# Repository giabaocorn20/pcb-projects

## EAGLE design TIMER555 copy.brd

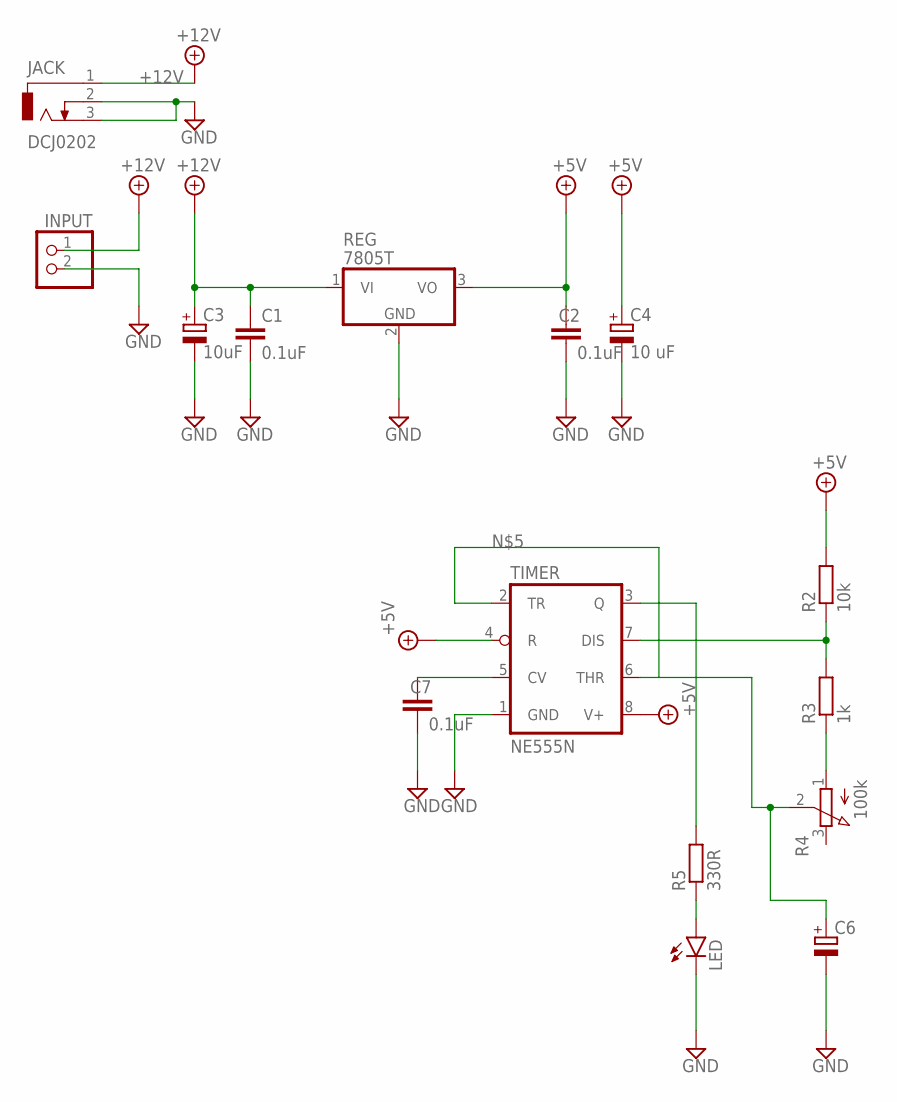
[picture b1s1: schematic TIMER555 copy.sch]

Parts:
C1, C2, C7: 0.1uF; C050-030X075
C3: 10uF; E3,5-8
C4: 10 uF; E3,5-8
C6: CPOL-EUE3.5-8; E3,5-8
INPUT: PINHD-1X2; 1X02
JACK: DCJ0202
LED: LED5MM
R2: 10k; 0207/10
R3: 1k; 0207/10
R4: 100k; 3RP/1610N
R5: 330R; 0207/10
REG: 7805T; TO220H
TIMER: NE555N; DIL08

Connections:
+5V: C2.1, C4.+, R2.2, REG.3 (VO), TIMER.4 (R), TIMER.8 (V+)
+12V: C1.1, C3.+, INPUT.1, JACK.1, REG.1 (VI)
GND: C1.2, C2.2, C3.-, C4.-, C6.-, C7.2, INPUT.2, JACK.2, JACK.3, LED.K (C), REG.2 (GND), TIMER.1 (GND)
unnamed: C7.1, TIMER.5 (CV)
unnamed: R2.1, R3.2, TIMER.7 (DIS)
unnamed: R3.1, R4.1 (A)
unnamed: C6.+, R4.2 (S), TIMER.2 (TR), TIMER.6 (THR)
unnamed: R5.2, TIMER.3 (Q)
unnamed: LED.A, R5.1

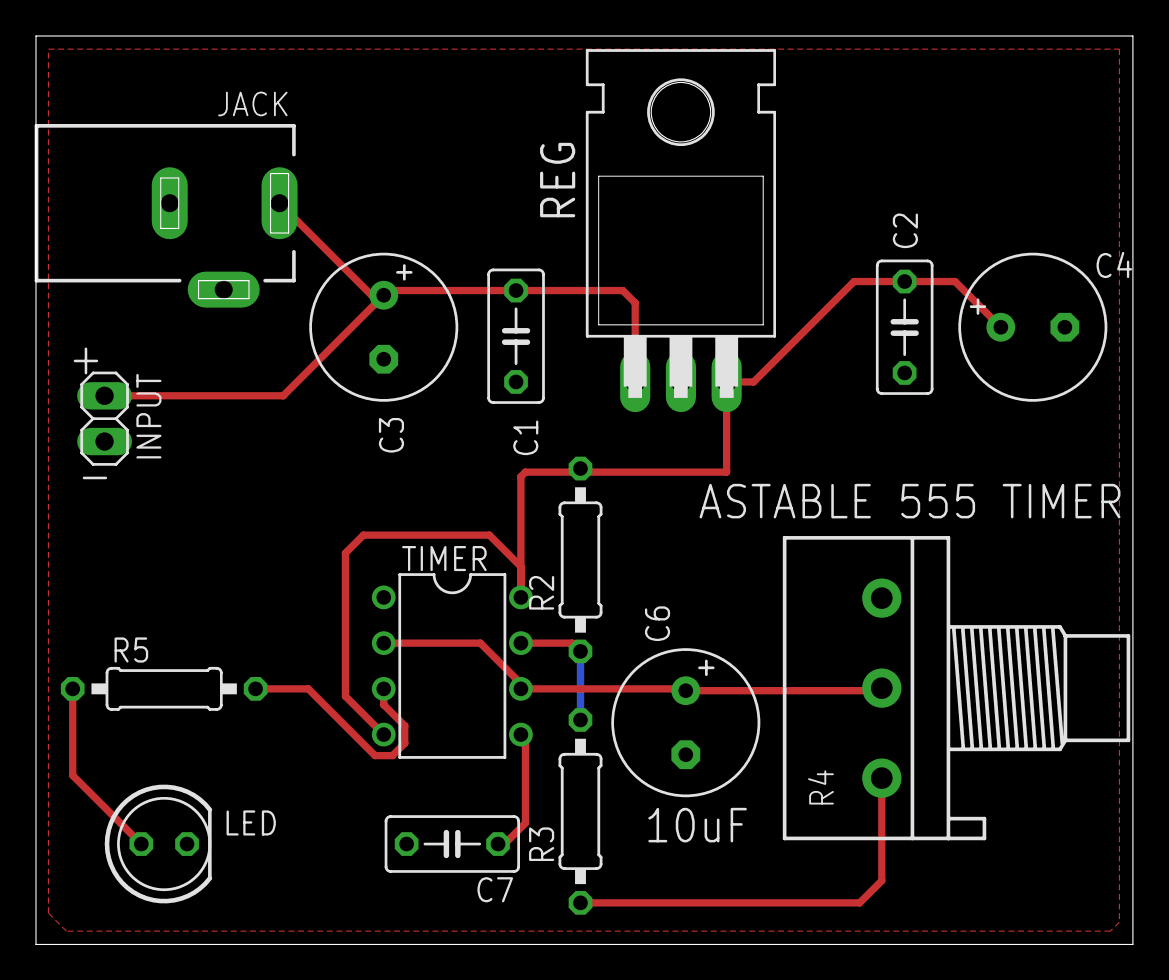
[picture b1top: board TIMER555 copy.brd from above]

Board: 2 copper layers, 60.9 x 50.5 mm, 15 parts (0 on the bottom side), 9 nets.

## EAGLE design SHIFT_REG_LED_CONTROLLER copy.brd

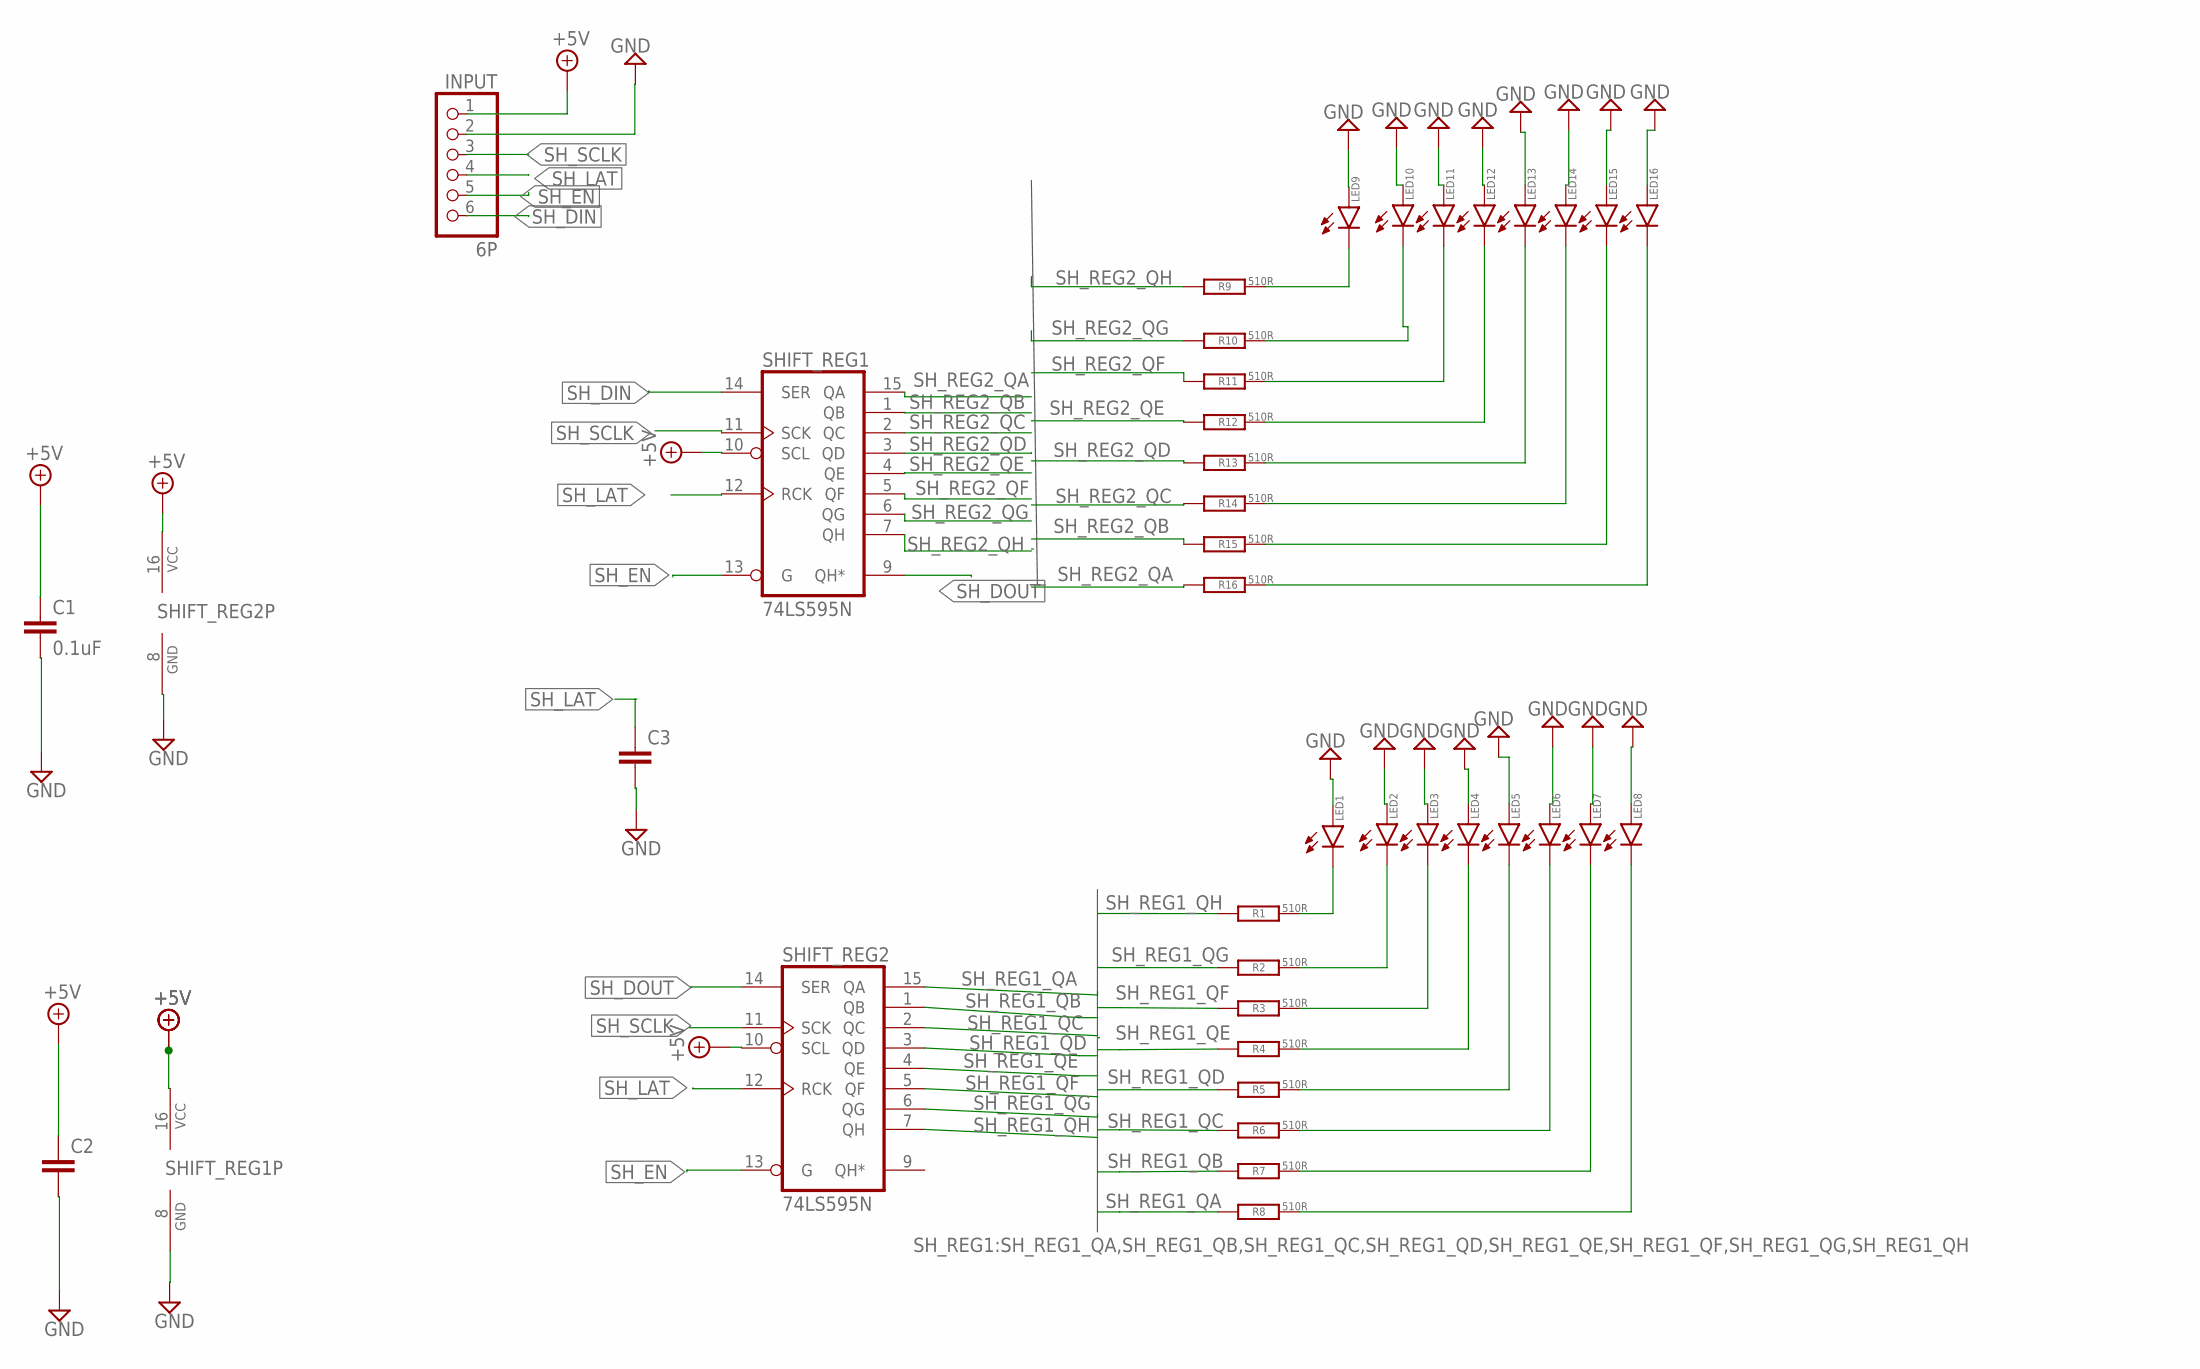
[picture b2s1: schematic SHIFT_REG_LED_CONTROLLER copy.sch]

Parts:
C1: 0.1uF; C050-030X075
C2, C3: C-EU050-030X075; C050-030X075
INPUT: 6P; 1X06
LED1, LED2, LED3, LED4, LED5, LED6, LED7, LED8, LED9, LED10, LED11, LED12, LED13, LED14, LED15, LED16: LED5MM
R1, R2, R3, R4, R5, R6, R7, R8, R9, R10, R11, R12, R13, R14, R15, R16: 510R; 0207/10
SHIFT_REG1, SHIFT_REG2: 74LS595N; DIL16

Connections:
+5V: C1.1, C2.1, INPUT.1, SHIFT_REG1.10 (SCL), SHIFT_REG1.16 (VCC), SHIFT_REG2.10 (SCL), SHIFT_REG2.16 (VCC)
GND: C1.2, C2.2, C3.2, INPUT.2, LED1.A, LED2.A, LED3.A, LED4.A, LED5.A, LED6.A, LED7.A, LED8.A, LED9.A, LED10.A, LED11.A, LED12.A, LED13.A, LED14.A, LED15.A, LED16.A, SHIFT_REG1.8 (GND), SHIFT_REG2.8 (GND)
unnamed: LED1.K (C), R1.2
unnamed: LED2.K (C), R2.2
unnamed: LED3.K (C), R3.2
unnamed: LED4.K (C), R4.2
unnamed: LED5.K (C), R5.2
unnamed: LED6.K (C), R6.2
unnamed: LED7.K (C), R7.2
unnamed: LED8.K (C), R8.2
unnamed: LED9.K (C), R9.2
unnamed: LED10.K (C), R10.2
unnamed: LED11.K (C), R11.2
unnamed: LED12.K (C), R12.2
unnamed: LED13.K (C), R13.2
unnamed: LED14.K (C), R14.2
unnamed: LED15.K (C), R15.2
unnamed: LED16.K (C), R16.2
SH_DIN: INPUT.6, SHIFT_REG1.14 (SER)
SH_DOUT: SHIFT_REG1.9 (QH*), SHIFT_REG2.14 (SER)
SH_EN: INPUT.5, SHIFT_REG1.13 (G), SHIFT_REG2.13 (G)
SH_LAT: C3.1, INPUT.4, SHIFT_REG1.12 (RCK), SHIFT_REG2.12 (RCK)
SH_REG1_QA: R8.1, SHIFT_REG2.15 (QA)
SH_REG1_QB: R7.1, SHIFT_REG2.1 (QB)
SH_REG1_QC: R6.1, SHIFT_REG2.2 (QC)
SH_REG1_QD: R5.1, SHIFT_REG2.3 (QD)
SH_REG1_QE: R4.1, SHIFT_REG2.4 (QE)
SH_REG1_QF: R3.1, SHIFT_REG2.5 (QF)
SH_REG1_QG: R2.1, SHIFT_REG2.6 (QG)
SH_REG1_QH: R1.1, SHIFT_REG2.7 (QH)
SH_REG2_QA: R16.1, SHIFT_REG1.15 (QA)
SH_REG2_QB: R15.1, SHIFT_REG1.1 (QB)
SH_REG2_QC: R14.1, SHIFT_REG1.2 (QC)
SH_REG2_QD: R13.1, SHIFT_REG1.3 (QD)
SH_REG2_QE: R12.1, SHIFT_REG1.4 (QE)
SH_REG2_QF: R11.1, SHIFT_REG1.5 (QF)
SH_REG2_QG: R10.1, SHIFT_REG1.6 (QG)
SH_REG2_QH: R9.1, SHIFT_REG1.7 (QH)
SH_SCLK: INPUT.3, SHIFT_REG1.11 (SCK), SHIFT_REG2.11 (SCK)

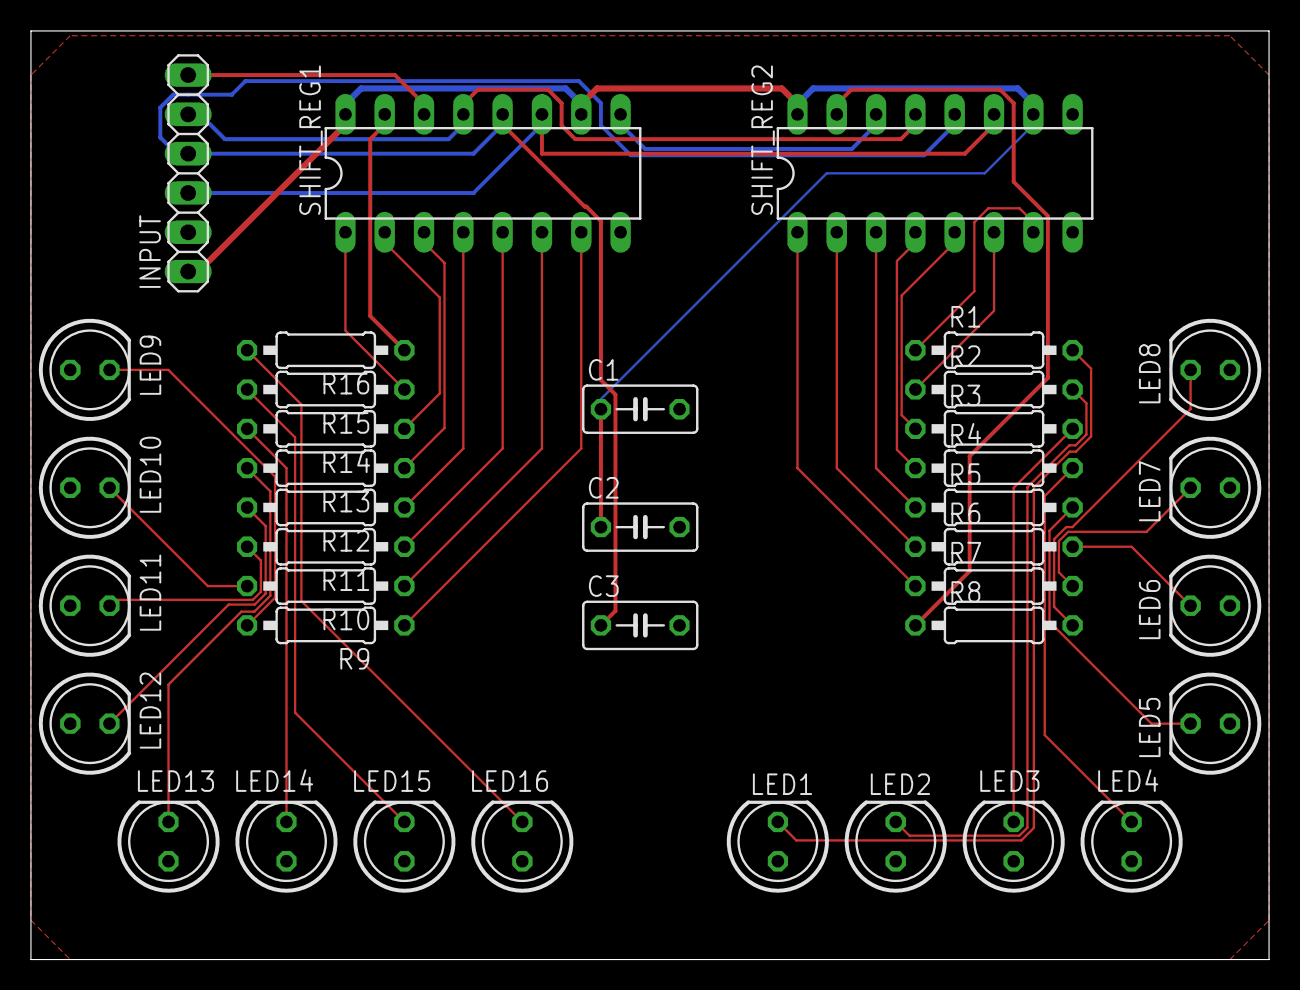
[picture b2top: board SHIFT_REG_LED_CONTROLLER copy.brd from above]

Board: 2 copper layers, 80.0 x 60.0 mm, 38 parts (0 on the bottom side), 39 nets.
